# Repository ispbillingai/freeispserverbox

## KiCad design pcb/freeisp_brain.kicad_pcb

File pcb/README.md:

# FreeISP brain board — KiCad project

Two-layer 100 × 100 mm carrier for the ESP32 and everything that lives with it
inside the module. Generated by `build.py`, routed by `router.py`, verified
with KiCad's own DRC.

Open `freeisp_brain.kicad_pcb` in KiCad 10 (PCB Editor). There is no schematic —
nets are declared in the board file, so the ratsnest and DRC work without one.

| | |
|---|---|
| Board | 100 × 100 mm, 1.6 mm FR-4, 2 layers |
| Clearance | 0.25 mm |
| Track width | 0.4 mm signal · 0.8–1.2 mm power |
| Vias | 17, Ø0.8 mm with 0.4 mm drill |
| Mounting | 4 × M3 Ø3.2, 4.5 mm in from each corner |
| DRC | **0 errors, 0 unconnected** |

## It is fully routed

`router.py` is a grid maze router. Obstacles are inflated by
`my_half + clearance + their_half` and any cell whose centre falls inside is
blocked, so KiCad's DRC agrees with it. The search runs over
`(cell, layer, heading)` with a turn penalty and a via penalty. Three orderings
are tried — power-first, shortest-first, longest-first — and whichever needs
fewest vias wins.

Every pad is through-hole, so a path may begin and end on either layer without
a via; a via on top of a pad would be redundant copper.

## ⚠ Nothing gets ordered until the paper test passes

**DRC does not check that a footprint matches a real part.** It checks
geometry. A board can be perfectly clean and still have the wrong number of
pins on a connector — that has already happened once here.

`fitcheck_1to1.pdf` is plotted at exact 1:1 scale.

1. Print it with scaling **off** (not "fit to page").
2. Measure the board outline — it must be exactly 100 × 100 mm. If it isn't,
   the printer scaled it and nothing else on the page is trustworthy.
3. Sit the **real ESP32, TFT, RC522 and MPU-6050** on their outlines. Every
   pin must land on its hole.
4. Check the terminal blocks and resistors the same way.

The ESP32 socket assumes **25.4 mm between the two pin rows** and a **30-pin**
board. Some clones use 22.86 mm, and 38-pin variants exist. This is the single
most expensive thing to get wrong.

## Modules that are wired, not plugged

The **LM2596 buck** and **TP4056 charger** have edge pads meant for wires, not
0.1″ headers. They bolt alongside the board and land on 4-way screw terminals:

- `U1` BUCK — IN+ · IN− · OUT+ · OUT−
- `U2` CHARGER — IN+ · IN− · B+ · B−

The 12 V feed is fused **inline in the wire**, not on the board.

## Still open

- **Firmware has no code yet for GPIO34 (mains sense), GPIO35 (battery
  sense) or GPIO13 (horn relay)** — those subsystems exist only as copper.
  Add the defines and reads to `LiveDashboardNext` before the first
  board-level test, or the new hardware is invisible.
- Set the LM2596 to **5.4–5.5 V** before wiring it in (review finding M1:
  at 5.0 V the battery boost can win the diode-OR and cycle the cell).
- J4 (5 V) and J5 (3.3 V) are identical 8-pin headers side by side — mark
  the plugs; a swap puts 5 V on the RC522.
- ESP32 pin map in `build.py` (`U3A_NETS` / `U3B_NETS`) is the standard 30-pin
  DevKit V1 order. Verify against your board's silkscreen.

An independent electrical review (2026-07-30) found two critical faults the
geometric checks could not see — a field "MAINS" pin wired bare into a 3.3 V
GPIO, and a horn return that connected to nothing. Both are fixed in rev E,
with the reverse-polarity diode, bulk capacitance and sense-line RC filters
from the same review. Lesson recorded: DRC + audit prove the copper matches
the netlist; only a circuit-level review proves the netlist is right.

## Warnings you can ignore

`lib_footprint_issues` × 23 — the embedded footprints have their library
version metadata stripped, so KiCad cannot match them to the library.
`silk_overlap` — reference designators touching; drag them if it bothers you.

## Regenerating

```
python build.py
"F:\kicad\bin\kicad-cli.exe" pcb drc --format json --output drc.json freeisp_brain.kicad_pcb
"F:\kicad\bin\kicad-cli.exe" pcb render --output board.png --side top freeisp_brain.kicad_pcb
"F:\kicad\bin\kicad-cli.exe" pcb export pdf --mode-single --output fitcheck_1to1.pdf --layers "F.Cu,F.SilkS,Edge.Cuts" --scale 1 --black-and-white freeisp_brain.kicad_pcb
```

`build.py` **overwrites** the board file. Once you edit anything in KiCad, stop
regenerating — or move the change into `build.py` first.

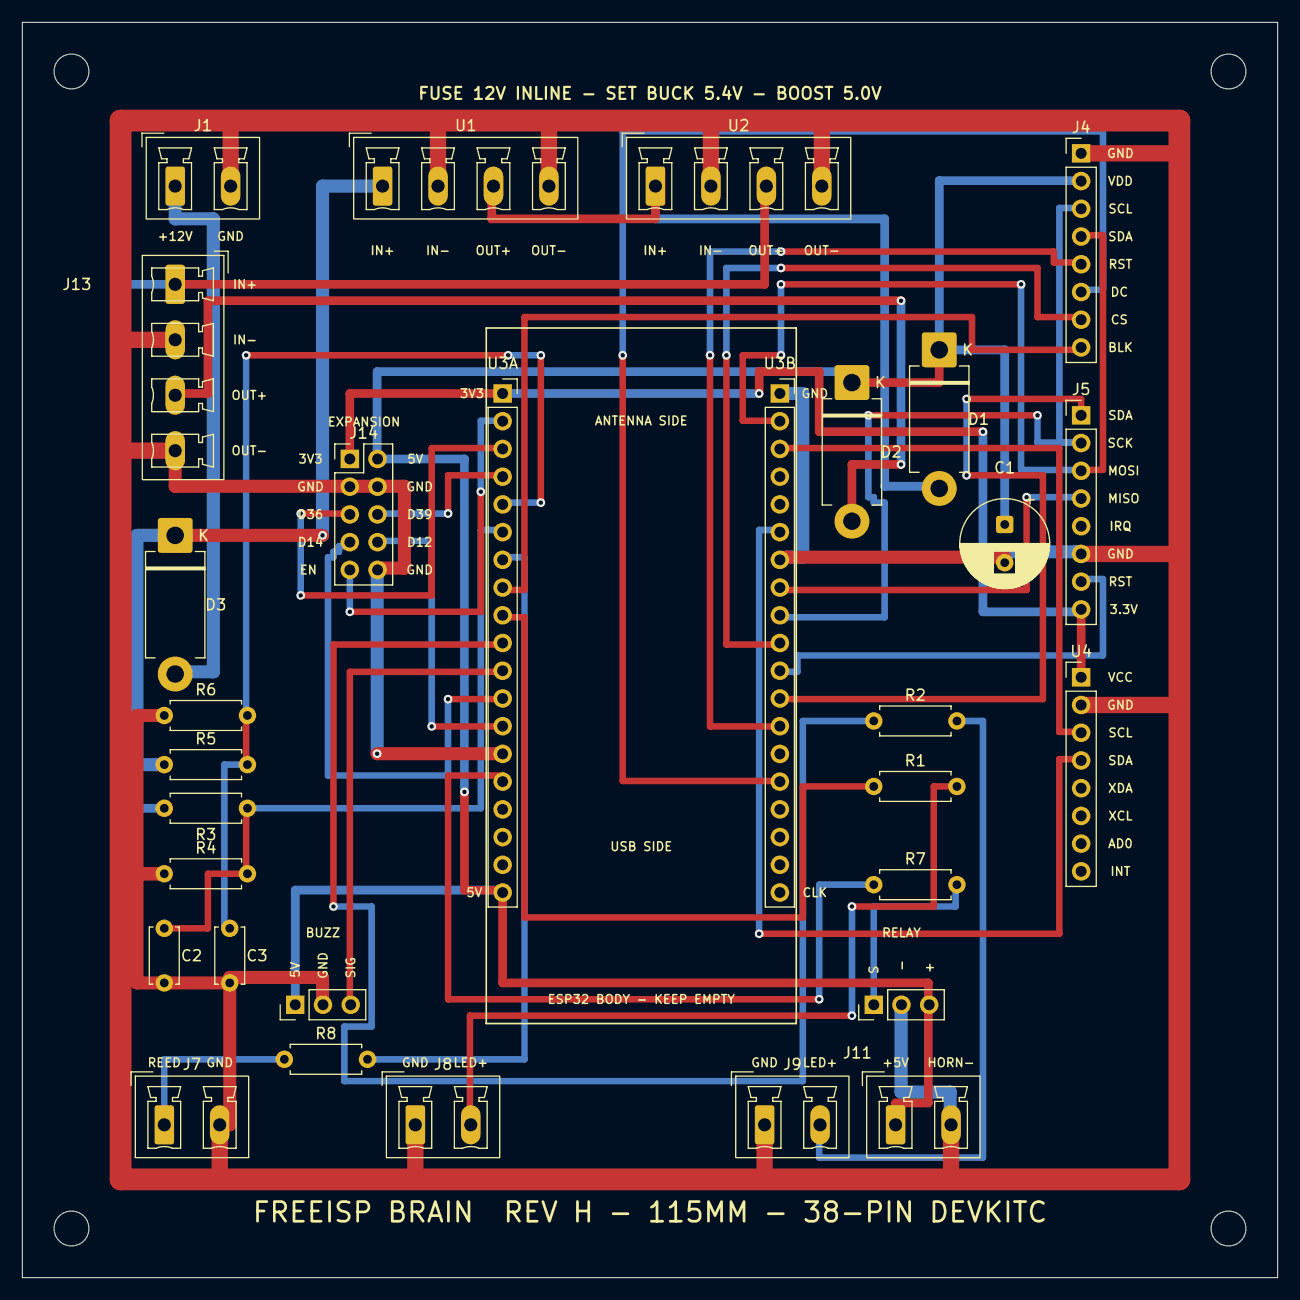
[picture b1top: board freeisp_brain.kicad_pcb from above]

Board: 2 copper layers, 115.0 x 115.0 mm, 34 parts (0 on the bottom side), 35 nets.

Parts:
C1: 470u; CP_Radial_D8.0mm_P3.50mm
C2, C3: 100n; C_Disc_D5.0mm_W2.5mm_P5.00mm
D1, D2, D3: 1N5822; D_DO-201AD_P12.70mm_Horizontal
H1, H2, H3, H4: M3; MountingHole_3.2mm_M3
J1: 12V IN; PhoenixContact_MCV_1,5_2-G-5.08_1x02_P5.08mm_Vertical
J4: TFT; PinHeader_1x08_P2.54mm_Vertical
J5: RC522; PinHeader_1x08_P2.54mm_Vertical
J7: REED; PhoenixContact_MCV_1,5_2-G-5.08_1x02_P5.08mm_Vertical
J8: LED R; PhoenixContact_MCV_1,5_2-G-5.08_1x02_P5.08mm_Vertical
J9: LED G; PhoenixContact_MCV_1,5_2-G-5.08_1x02_P5.08mm_Vertical
J10: BUZZER; PinHeader_1x03_P2.54mm_Vertical
J11: HORN; PhoenixContact_MCV_1,5_2-G-5.08_1x02_P5.08mm_Vertical
J13: BOOST IN+ IN- OUT+ OUT-; PhoenixContact_MCV_1,5_4-G-5.08_1x04_P5.08mm_Vertical
J14: EXPANSION; PinHeader_2x05_P2.54mm_Vertical
K1: HORN RLY; PinHeader_1x03_P2.54mm_Vertical
R1, R2: 220R; R_Axial_DIN0207_L6.3mm_D2.5mm_P7.62mm_Horizontal
R3, R4, R5: 100k; R_Axial_DIN0207_L6.3mm_D2.5mm_P7.62mm_Horizontal
R6: 27k; R_Axial_DIN0207_L6.3mm_D2.5mm_P7.62mm_Horizontal
R7, R8: 1k; R_Axial_DIN0207_L6.3mm_D2.5mm_P7.62mm_Horizontal
U1: BUCK IN+ IN- OUT+ OUT-; PhoenixContact_MCV_1,5_4-G-5.08_1x04_P5.08mm_Vertical
U2: CHARGER IN+ IN- OUT+ OUT-; PhoenixContact_MCV_1,5_4-G-5.08_1x04_P5.08mm_Vertical
U3A: ESP32 L; PinSocket_1x19_P2.54mm_Vertical
U3B: ESP32 R; PinSocket_1x19_P2.54mm_Vertical
U4: MPU-6050; PinHeader_1x08_P2.54mm_Vertical

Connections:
+3V3: J5.8, J14.1, U3A.1, U4.1
+5V: D1.2, U1.3, U2.1
+5V_BAT: D2.2, J13.3
+5V_SYS: C1.1, D1.1, D2.1, J4.2, J10.1, J11.1, J14.2, K1.3, U3A.19
+12V: D3.1, R5.1, U1.1
+12V_IN: D3.2, J1.1
BUZZ: J10.3, U3A.11
EXP_D12: J14.8, U3A.13
EXP_D14: J14.7, U3A.12
EXP_D36: J14.5, U3A.3
EXP_D39: J14.6, U3A.4
EXP_EN: J14.9, U3A.2
GND: C1.2, C2.2, C3.2, J1.2, J4.1, J5.6, J7.2, J8.1, J9.1, J10.2, J11.2, J13.2, J13.4, J14.3, J14.4, J14.10, K1.2, R4.1, R6.1, U1.2, U1.4, U2.2, U2.4, U3A.14, U3B.1, U3B.7, U4.2
HORN_DRV: K1.1, R7.2
HORN_IN: R7.1, U3A.15
LED_G: R2.1, U3A.10
LED_G_A: J9.2, R2.2
LED_R: R1.1, U3A.9
LED_R_A: J8.2, R1.2
MISO: J5.4, U3B.8
MOSI: J4.4, J5.3, U3B.2
RC_RST: J5.7, U3B.11
RC_SS: J5.1, U3B.12
REED: R8.2, U3A.7
REED_F: J7.1, R8.1
SCK: J4.3, J5.2, U3B.9
SCL: U3B.3, U4.3
SDA: U3B.6, U4.4
SENSE_BATT: C2.1, R3.2, R4.2, U3A.6
SENSE_MAINS: C3.1, R5.2, R6.2, U3A.5
TFT_BLK: J4.8, U3A.8
TFT_CS: J4.7, U3B.10
TFT_DC: J4.6, U3B.15
TFT_RST: J4.5, U3B.13
VBAT: J13.1, R3.1, U2.3

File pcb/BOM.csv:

Item,Qty,Designators,Description,Notes
1,2,C2 C3,Ceramic capacitor 100nF,5mm disc
2,1,C1,Electrolytic capacitor 470uF 16V,"8mm dia, 3.5mm pitch"
3,2,U3A U3B,"Female header socket 1x19, 2.54mm",cut from a 40-pin strip
4,1,J10,"Male pin header 1x3, 2.54mm",buzzer
5,1,K1,"Male pin header 1x3, 2.54mm",relay control
6,1,U4,"Male pin header 1x8, 2.54mm",MPU-6050 socket
7,1,J5,"Male pin header 1x8, 2.54mm",RC522 socket
8,1,J4,"Male pin header 1x8, 2.54mm",TFT socket
9,1,J14,"Male pin header 2x5, 2.54mm",EXPANSION
10,1,R5,Resistor 100k 1/4W,12V divider
11,2,R3 R4,Resistor 100k 1/4W,battery divider
12,1,R8,Resistor 1k 1/4W,reed input
13,1,R7,Resistor 1k 1/4W,relay drive
14,1,R2,Resistor 220R 1/4W,green LED
15,1,R1,Resistor 220R 1/4W,red LED
16,1,R6,Resistor 27k 1/4W,12V divider
17,3,D1 D2 D3,Schottky diode 3A DO-201AD,1N5822 (or SR340/SB360)
18,5,J1 J11 J7 J8 J9,Screw terminal 2-way 5.08mm,"KF301 / MCV 1,5-2-G-5.08"
19,3,J13 U1 U2,Screw terminal 4-way 5.08mm,"KF301 / MCV 1,5-4-G-5.08"

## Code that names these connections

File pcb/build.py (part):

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ESP_ROW = 25.4
U3A_NETS = {
    1: "+3V3",       # 3V3 is top-LEFT on the 38-pin board
    5: "SENSE_MAINS",   # GPIO34
    6: "SENSE_BATT",    # GPIO35
    7: "REED",          # GPIO32
    8: "TFT_BLK",       # GPIO33
    9: "LED_R",         # GPIO25
    10: "LED_G",        # GPIO26
    11: "BUZZ",         # GPIO27
    14: "GND",
    15: "HORN_IN",      # GPIO13
    19: "+5V_SYS",      # 5V/VIN, bottom-left -- eats from whichever diode wins
    # --- spares brought out to J14, so a later idea needs no new board ---
    2: "EXP_EN",        # reset: a button to GND reboots the box
    3: "EXP_D36",       # VP  - input ONLY, ADC1, no internal pull-up
    4: "EXP_D39",       # VN  - input ONLY, ADC1, no internal pull-up
    12: "EXP_D14",      # a full GPIO with an internal pull-up: best for buttons
    13: "EXP_D12",      # strapping pin - must be LOW at boot
}
U3B_NETS = {
    1: "GND",
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    7: "GND",
    8: "MISO",          # GPIO19
    9: "SCK",           # GPIO18
    10: "TFT_CS",       # GPIO5
    11: "RC_RST",       # GPIO17
    12: "RC_SS",        # GPIO16
    13: "TFT_RST",      # GPIO4
    15: "TFT_DC",       # GPIO2
}

PARTS = {
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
